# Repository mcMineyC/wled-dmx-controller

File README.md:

# wled-dmx-controller
A DMX controller with WLED built in

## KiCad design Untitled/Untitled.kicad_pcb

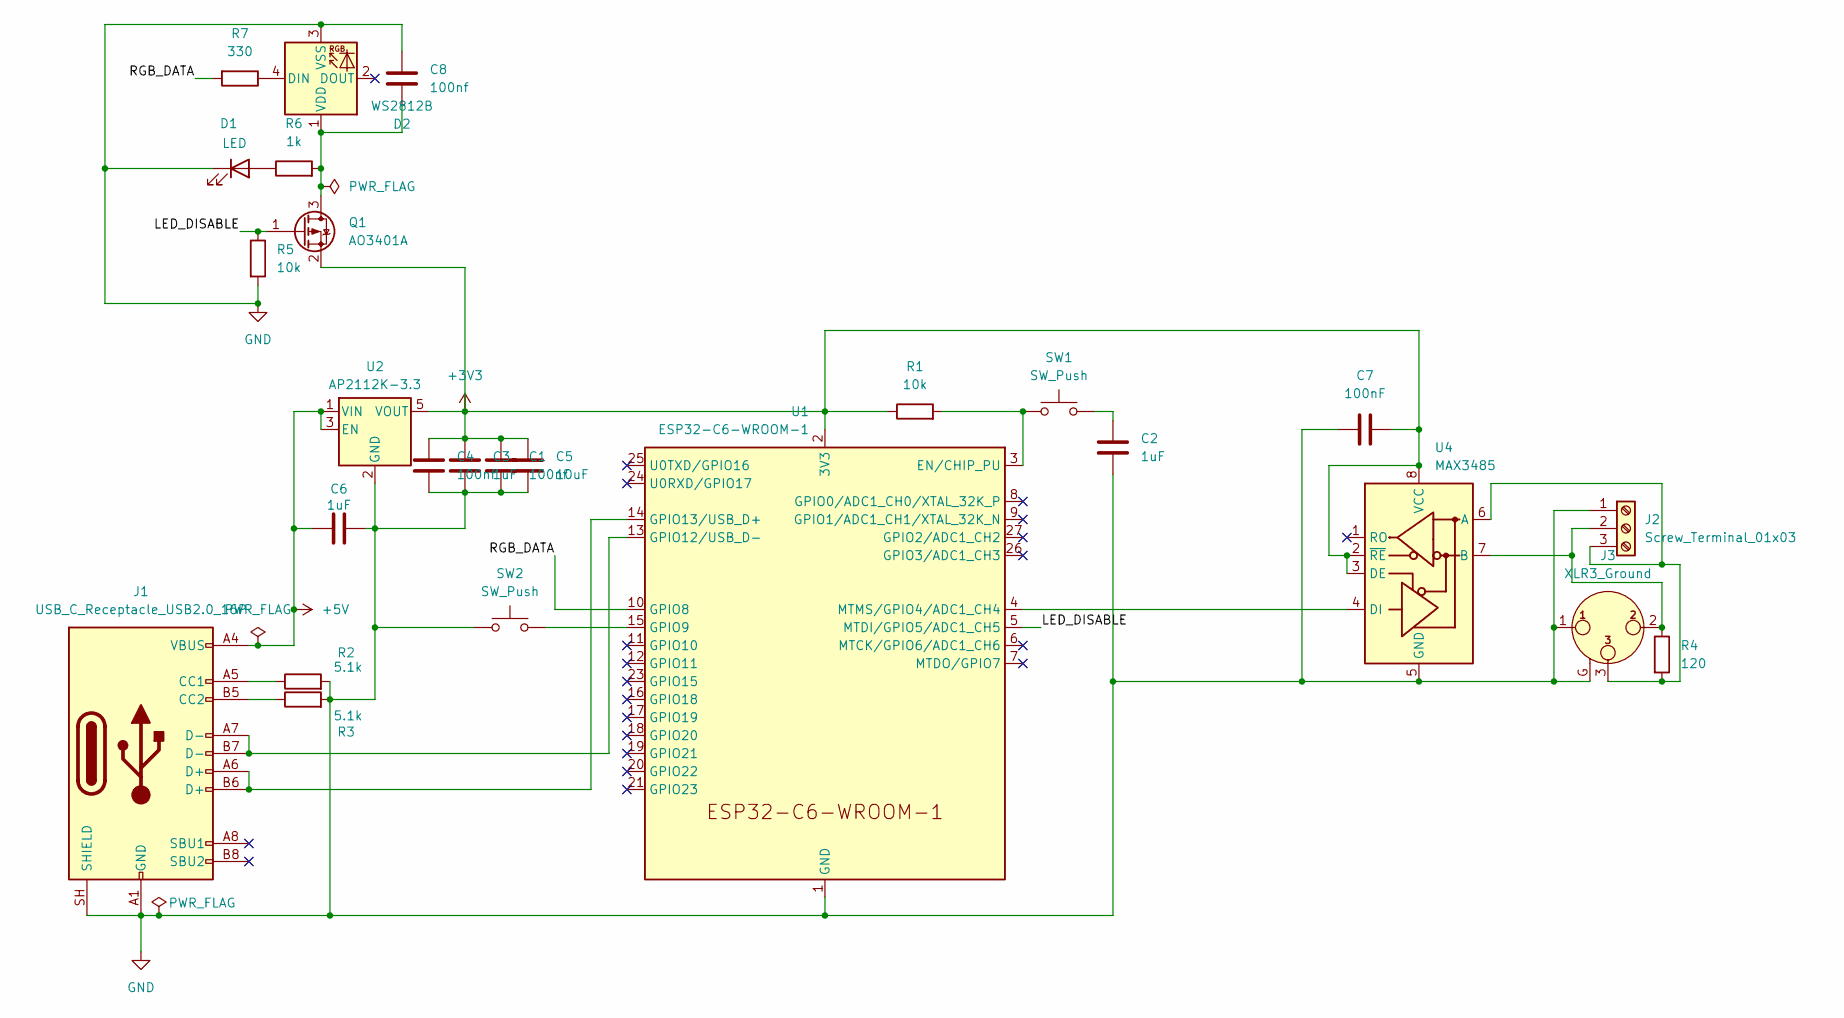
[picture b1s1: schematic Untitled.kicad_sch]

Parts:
C1, C4, C8: 100nf; C_0805_2012Metric
C2, C3, C6: 1uF; C_0805_2012Metric
C5: 10uF; C_0805_2012Metric
C7: 100nF; C_0805_2012Metric
D1: LED; LED_0805_2012Metric
D2: WS2812B; LED_WS2812B_PLCC4_5.0x5.0mm_P3.2mm
J1: USB_C_Receptacle_USB2.0_16P; USB_C_Receptacle_GCT_USB4105-xx-A_16P_TopMnt_Horizontal
J2: Screw_Terminal_01x03; TerminalBlock_Phoenix_MKDS-1,5-3-5.08_1x03_P5.08mm_Horizont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
J3: XLR3_Ground; Jack_XLR_Neutrik_NC3FAH2_Horizontal
Q1: AO3401A; SOT-23
R1, R5: 10k; R_0805_2012Metric
R2, R3: 5.1k; R_0805_2012Metric
R4: 120; R_0805_2012Metric
R6: 1k; R_0805_2012Metric
R7: 330; R_0805_2012Metric
SW1, SW2: SW_Push; SW_SPST_TL3342
U1: ESP32-C6-WROOM-1
U2: AP2112K-3.3; SOT-23-5
U4: MAX3485; SOIC-8_3.9x4.9mm_P1.27mm

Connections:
+3V3: C1.1, C3.1, C4.1, C5.1, C7.2, Q1.2 (S), R1.1, U1.2 (3V3), U2.5 (VOUT), U4.2 (~RE), U4.3 (DE), U4.8 (VCC)
+5V: C6.2, J1.A4 (VBUS), J1.A9 (VBUS), J1.B4 (VBUS), J1.B9 (VBUS), U2.1 (VIN), U2.3 (EN)
/LED_DISABLE: Q1.1 (G), R5.1, U1.5 (MTDI/GPIO5/ADC1_CH5)
/RGB_DATA: R7.2, U1.10 (GPIO8)
GND: C1.2, C2.2, C3.2, C4.2, C5.2, C6.1, C7.1, C8.1, D1.1 (K), D2.3 (VSS), J1.A1 (GND), J1.A12 (GND), J1.B1 (GND), J1.B12 (GND), J1.SH (SHIELD), J2.1, J3.1, J3.G, R2.2, R3.2, R5.2, SW2.1, U1.1 (GND), U1.28 (GND), U1.29 (GND), U2.2 (GND), U4.5 (GND)
unnamed: C2.1, SW1.2
unnamed: D1.2 (A), R6.1
unnamed: D2.4 (DIN), R7.1
unnamed: C8.2, D2.1 (VDD), Q1.3 (D), R6.2
unnamed: J1.A5 (CC1), R2.1
unnamed: J1.B5 (CC2), R3.1
unnamed: J2.2, J3.2, R4.1, U4.7 (B)
unnamed: J2.3, J3.3, R4.2, U4.6 (A)
unnamed: R1.2, SW1.1, U1.3 (EN/CHIP_PU)
unnamed: SW2.2, U1.15 (GPIO9)
unnamed: J1.A7 (D-), J1.B7 (D-), U1.13 (GPIO12/USB_D-)
unnamed: J1.A6 (D+), J1.B6 (D+), U1.14 (GPIO13/USB_D+)
unnamed: U1.4 (MTMS/GPIO4/ADC1_CH4), U4.4 (DI)

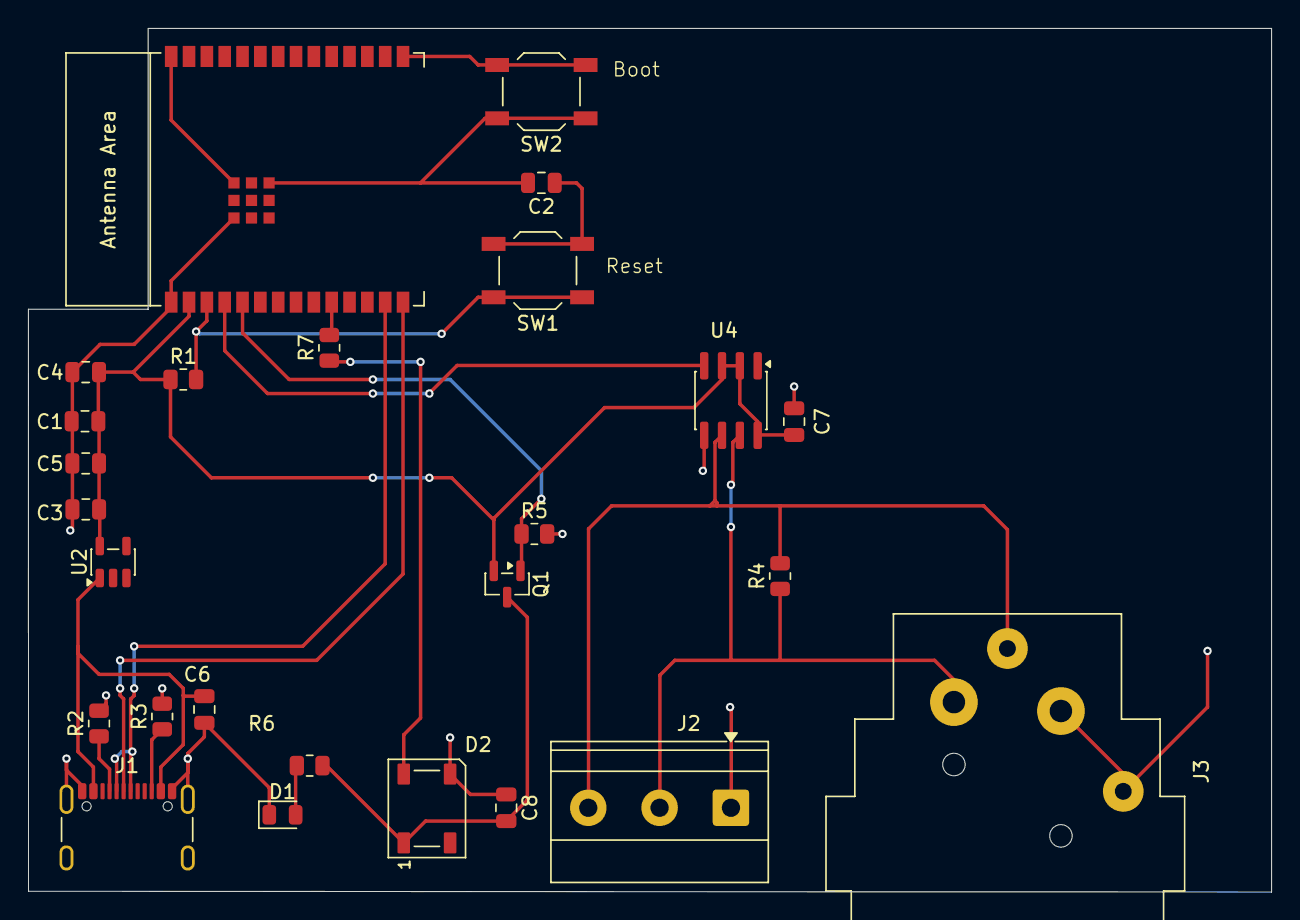
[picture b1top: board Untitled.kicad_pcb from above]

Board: 2 copper layers, 88.5 x 61.5 mm, 26 parts (0 on the bottom side), 18 nets.
